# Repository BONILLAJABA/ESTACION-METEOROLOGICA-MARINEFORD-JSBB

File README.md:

# ESTACION-METEOROLOGICA-MARINEFORD-JSBB
Este repositorio muestra un proyecto de investigación del diseño y construcción de una estación meteorológica  utilizando comunicación serial con el micro-controlador ARDUINO UNO y protocolo ethernet.

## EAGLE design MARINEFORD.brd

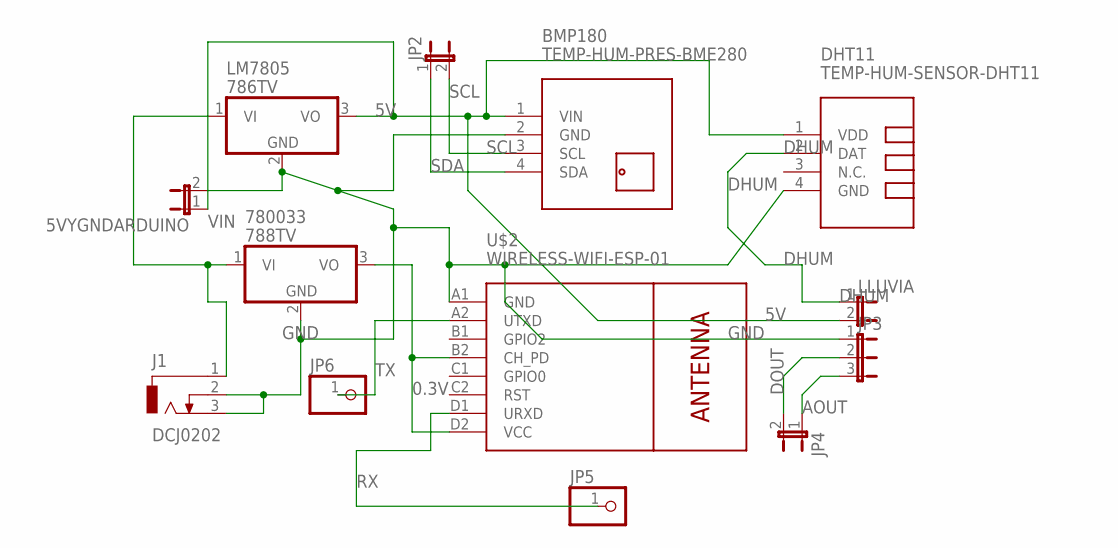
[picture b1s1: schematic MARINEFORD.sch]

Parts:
5VYGNDARDUINO: JP1E; JP1
780033: 788TV; TO220V
BMP180: TEMP-HUM-PRES-BME280
DHT11: TEMP-HUM-SENSOR-DHT11
J1: DCJ0202
JP2, JP4: JP1E; JP1
JP3: JP2E; JP2
JP5, JP6: PINHD-1X1; 1X01
LLUVIA: JP1E; JP1
LM7805: 786TV; TO220V
U$2: WIRELESS-WIFI-ESP-01

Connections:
0.3V: 780033.3 (VO), U$2.B2 (CH_PD), U$2.D2 (VCC)
5V: 5VYGNDARDUINO.1, BMP180.1 (VIN), DHT11.1 (VDD), LLUVIA.2, LM7805.3 (VO)
AOUT: JP3.3, JP4.1
DHUM: DHT11.2 (DAT), LLUVIA.1
DOUT: JP3.2, JP4.2
GND: 5VYGNDARDUINO.2, 780033.2 (GND), BMP180.2 (GND), DHT11.4 (GND), J1.2, J1.3, JP3.1, LM7805.2 (GND), U$2.A1 (GND)
RX: JP5.1, U$2.D1 (URXD)
SCL: BMP180.3 (SCL), JP2.2
SDA: BMP180.4 (SDA), JP2.1
TX: JP6.1, U$2.A2 (UTXD)
VIN: 780033.1 (VI), J1.1, LM7805.1 (VI)

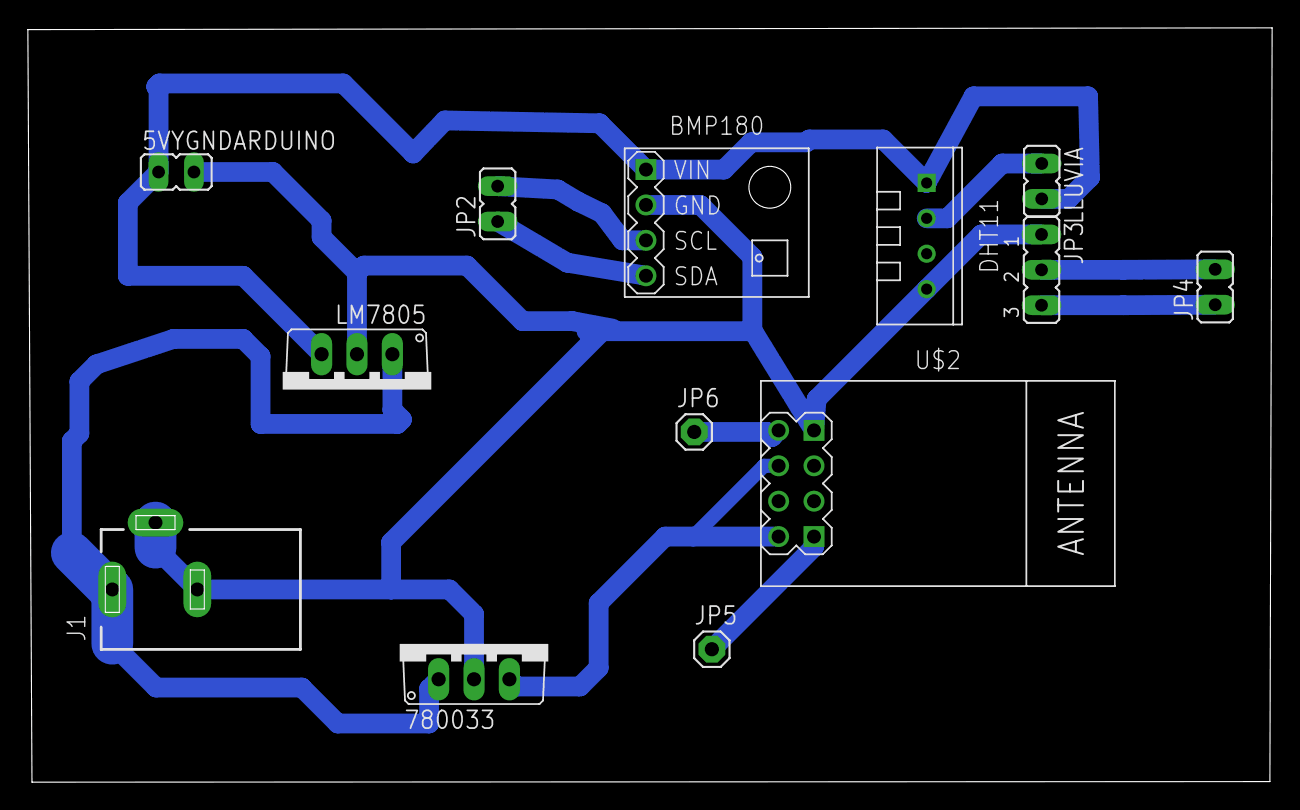
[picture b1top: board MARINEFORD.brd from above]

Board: 2 copper layers, 89.3 x 54.1 mm, 13 parts (0 on the bottom side), 11 nets.

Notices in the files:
parts and their libraries:
BME280: Released under the Creative Commons Attribution 4.0 International License: http://creativecommons.org/licenses/by/4.0
